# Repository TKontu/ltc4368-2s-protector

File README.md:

# DC2418-LVC — 2S LiPo/LiHV Low-Voltage Cutoff & Protection Board

An inline protection board for replacing 2S NiMH/NiCd packs with 2S LiPo/LiHV, built around the
Analog Devices **LTC4368-1**. NiMH tolerates being run flat; LiPo/LiHV does not. This board adds
the low-voltage cutoff those older packs never needed, plus reverse-battery and bidirectional
overcurrent protection, between the battery and the existing load.

Pack-total sensing on the two main leads only — cell balancing is handled by the charger via the
balance lead. Adapted from the ADI **DC2418A** demo board, rescaled from 24 V / 10 A to a 2S
(6.0–8.7 V) pack.

> **Status:** built and bench-tested (smoke-stopper current-limited first power-up) on the current
> revision.

| Front (F.Cu) | Back (B.Cu) |
|---|---|
|  |  |

Board outline **60.0 × 33.5 mm**, 2 layers, XT30PW-M (VIN) and XT30PW-F (VOUT) horizontal
connectors, 4× M5.5 mounting holes.

## Features

- Under-voltage cutoff (LVC), over-voltage backstop
- Bidirectional overcurrent circuit breaker (fast, resettable)
- Reverse-battery protection (back-to-back N-FETs)
- ~4–10 µA quiescent; enable pin can be switched for µA-level off
- Auto-retry or latch-off, selectable by the RETRY cap

## Specifications (as configured)

| Parameter | Value | Set by |
|---|---|---|
| Battery | 2S LiPo / LiHV (7.4 / 7.6 V nom) | — |
| Input range | 6.0 – 8.7 V (chip: 2.5–60 V) | — |
| Under-voltage cutoff | 6.36 V (3.18 V/cell) under load | R7/R1/R2/R3 |
| Over-voltage cutoff | ~9.9 V | R7/R1/R2/R3 |
| Overcurrent trip | ~42 A fwd & rev | R4 = 1.2 mΩ |
| OC response | Auto-retry (~1.3 s) | C5 = 0.22 µF |
| Quiescent | ~4–10 µA (op), <3 µA (shutdown) | — |

Thresholds are ratios against the LTC4368's 0.5 V references, so only ratios matter:

```
V_UV   = 0.5 x (R7+R1+R2+R3) / (R2+R3)   -> 6.36 V
V_OV   = 0.5 x (R7+R1+R2+R3) / R3        -> 9.9 V
I_trip = 0.050 / R4                       -> ~42 A at 1.2 mohm
```

For 3.0 V/cell set `V_UV = 6.0 V`; for a different breaker point `R4 = 0.050 / I_trip`.

## Repository contents

```
DC2418-LVC-end/             KiCad project + Gerbers; XT30 connectors at the board ends
  DC2418A-2.kicad_sch / .kicad_pcb / .kicad_pro
  DC2418A-2-*.gbr / *.drl / *-job.gbrjob    Fabrication outputs (Gerber X2 + Excellon)
DC2418-LVC-side/            Electrically identical; XT30 connectors to the side
  LVC.kicad_sch / .kicad_pcb / .kicad_pro
  LVC-*.gbr / *.drl / *-job.gbrjob          Fabrication outputs
BOM.csv                     LCSC-referenced bill of materials
front.png / back.png        Layout views of DC2418-LVC-end
```

## Bill of materials

| Ref | Value / Part | Package | Notes |
|---|---|---|---|
| U1 | LTC4368CMS-1 | MSOP-10 | Use **I**-grade (LTC4368IMS-1) for sub-zero use |
| Q2, Q3 | SiR870ADP (or IRLR7843 in DPAK) | PDFN-8 5×6 | Back-to-back N-FETs; PDFN has a thermal pad |
| R4 | **1.2 mΩ ≥1 W, alloy/current-sense** | 2512 | Overcurrent set point — must be a metal-element part |
| R7 | 649 kΩ 1% | 0603 | Divider (SHDN tap) |
| R1 | 1.18 MΩ 1% | 0603 | Divider (UV tap) |
| R2 | 56.2 kΩ 1% | 0603 | Divider (OV tap) |
| R3 | 100 kΩ 1% | 0603 | Divider (bottom) |
| R13 | 22 kΩ | 1206 | Gate inrush resistor |
| C11 | 3.3 nF | 1206 | Gate inrush cap (soft-start) |
| C5 | 0.22 µF | 0603 | RETRY → auto-retry (GND = latch-off) |
| C15 | 1 µF | 1206 | VIN bypass (place at the pin) |
| C7 | 4.7 µF (optional) | 2220 | Input bulk cap |
| C1 | 47 µF ≥25 V | THT radial, **D8.0 mm body / 3.5 mm pitch** | Output bulk cap — footprint is `CP_Radial_D8.0mm_P3.80mm` |
| C2, C6 | 4.7 µF | 1210 | Output caps |

Divider values are E96 1%. Cap voltage ratings are inherited 100 V parts; **25 V is sufficient**
for a 2S pack.

> **Not in the BOM:** the **XT30 connectors are not listed** — both boards place an
> `AMASS_XT30PW-M` (VIN) and an `AMASS_XT30PW-F` (VOUT), source them separately. The
> bidirectional **TVS** recommended under [Usage](#usage) is also not listed.
>
> **Do not populate:** **R5** (2512) — the DC2418A's version-option pair with R4. On the **-A**
> build, R4 is the live sense position (1.2 mΩ); R5 is the **-B**'s 0.02 Ω slot. Verified: R4 and
> R5 bridge the same two nodes (`VOUT` ↔ `Net-(U1-SENSE)`), i.e. **parallel alternates, not in
> series** — so leaving R5 empty is harmless. Also `C9` and `C10`, both marked `OPT`.

## Build notes

- **2-layer board.** Keep VIN → Q2 → Q3 → R4 → VOUT short and wide; **2 oz copper** on that path.
- **Kelvin-sense R4:** route SENSE and VOUT to the resistor's own pads, not the current trace.
- **Q2/Q3 PDFN** have a bottom thermal pad. The footprints on both boards include it as pad 5 (drain:
  VIN on Q2, SENSE on Q3) with a paste opening. Without it, solder wicks under the large exposed pad
  and pulls the FET off its small pins. Needs hot-air/reflow with paste, not an iron. Swap to
  DPAK (IRLR7843) for iron/heat-gun assembly (footprint changes; keep sources common, drains out).
- Before power-up, net-highlight two nets: the **FET common-source node** (both sources, not a
  drain) and the **UV/OV tap order** (UV taps *above* OV).

## Usage

- Wire **battery → VIN/GND** and **VOUT/GND → the existing load input** (not across a motor directly).
- Fit a **bidirectional TVS across VOUT–GND** to clamp the inductive kick when the breaker opens.
- **Charge externally** on a balance charger set to the right chemistry (LiHV vs LiPo). Never charge
  through this board — it does not charge or balance.

## ⚠️ Safety

Discharge-side protection only. LiPo/LiHV is hazardous if abused — charge on a proper balance
charger in a fireproof location, never unattended. Provided **as-is, without warranty**; verify in
your own application.

## Provenance & license

Topology adapted from Analog Devices' **DC2418A** demo board for the LTC4368; independently
re-drawn schematic and layout, not affiliated with or endorsed by ADI.

Hardware (schematics, layout, Gerbers): **[CERN-OHL-S-2.0](LICENCE)** — strongly reciprocal.
Documentation (this README, BOM, images): **[CC-BY-4.0](LICENSE-docs)**.

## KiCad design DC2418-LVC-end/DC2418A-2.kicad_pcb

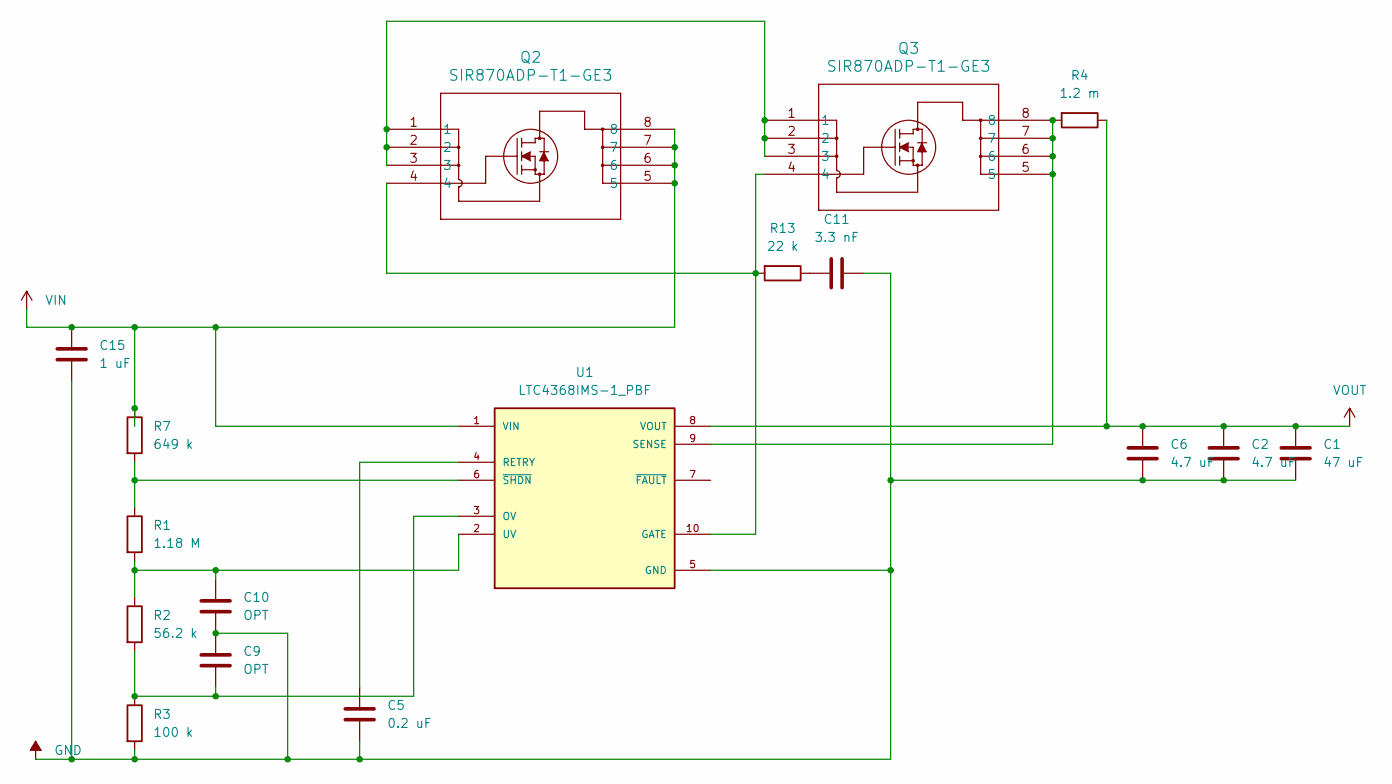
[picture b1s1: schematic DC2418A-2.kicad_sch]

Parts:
C1: 47 uF
C2, C6: 4.7 uF
C5: 0.2 uF
C9, C10: OPT
C11: 3.3 nF
C15: 1 uF
Q2, Q3: SIR870ADP-T1-GE3; POWERPAK_SO-8_SINGLE_VIS
R1: 1.18 M
R2: 56.2 k
R3: 100 k
R4: 1.2 m
R7: 649 k
R13: 22 k
U1: LTC4368IMS-1_PBF; SOP50P490X110-10N; PARTREV F

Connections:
GND: C1.2, C2.2, C5.2, C6.2, C9.1, C10.2, C11.1, C15.2, R3.2, U1.5 (GND); also elsewhere on the board
unnamed: C11.2, R13.1
unnamed: Q2.1, Q2.2, Q2.3, Q3.1, Q3.2, Q3.3
unnamed: Q2.4, Q3.4, R13.2, U1.10 (GATE)
unnamed: C9.2, R2.2, R3.1, U1.3 (OV)
unnamed: C5.1, U1.4 (RETRY)
unnamed 6: Q3.5, Q3.6, Q3.7, Q3.8, R4.2, U1.9 (SENSE); also elsewhere on the board
unnamed: C10.1, R1.2, R2.1, U1.2 (UV)
unnamed: R1.1, R7.2, U1.6 (~SHDN)
VIN: C15.1, Q2.5, Q2.6, Q2.7, Q2.8, R7.1, U1.1 (VIN); also elsewhere on the board
VOUT: C1.1, C2.1, C6.1, R4.1, U1.8 (VOUT); also elsewhere on the board

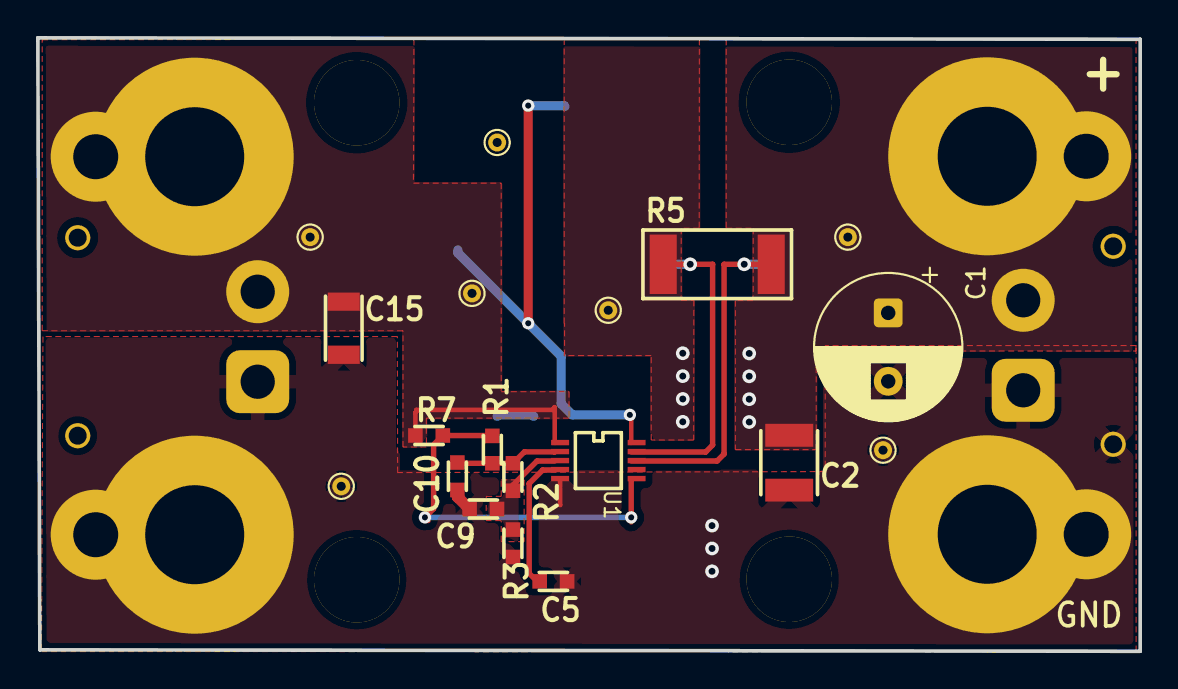
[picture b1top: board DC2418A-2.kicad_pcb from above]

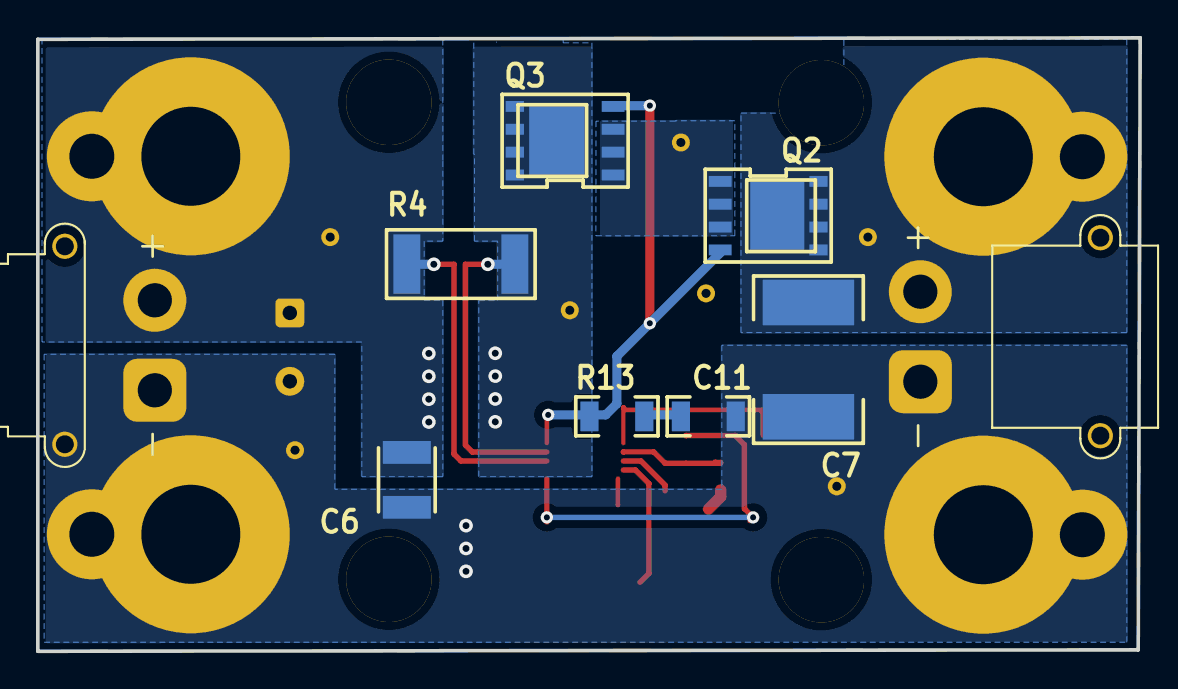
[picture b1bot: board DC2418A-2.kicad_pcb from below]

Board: 2 copper layers, 61.2 x 34.1 mm, 23 parts (7 on the bottom side), 11 nets.

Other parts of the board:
C7: 4.7 uF; 2220
MH3, MH4, MH5, MH6: KEYSTONE_8831
R5: DNP; 2512

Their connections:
GND: C7.2; also elsewhere on the board
unnamed 6: R5.2; also elsewhere on the board
VIN: C7.1; also elsewhere on the board
VOUT: R5.1; also elsewhere on the board
